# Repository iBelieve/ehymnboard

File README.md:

# eHymnBoard

A digital hymn board using e-ink screens. Designed and built by Michael Spencer and Christopher Spencer. First used in the Divine Service on Easter Sunday, A+D 2025.

This was a really interesting opportunity to explore how we might leverage modern technology in an anti-technology, anti-screens way. Hymn boards are a beautiful contrast to the modern trend of putting big distracting glowing screens in the front of the sanctuary by directing the congregation to a hymnal, a physical book with a collection of beloved time-tested hymns, a book that belongs not just in the sanctuary but in the home for daily family devotions.

The e-ink is as minimally distracting as possible. The screens have no light and do not glow at all; the e-ink particles combined with a matte finish makes them look "real" and "physical" and not digital or screen-like.They are updated once before the service and are literally powered off for the entire duration of the service (due to its physical nature, e-ink "holds" its content without power).

Looking for other projects that explore how modern technology can enhance tradition? Check out the [St. Martin Luther Zimbelstern](https://github.com/cmspencer109/Zimbelstern) by Christopher Spencer.

### Project Parts and Tech Stack

**Device**

The on-device code is responsible for driving the e-ink screens and handling the network communication with the server.

- Raspberry Pi Pico W
- [3x Waveshare 13.3" E-Paper HAT (K)](https://www.waveshare.com/product/ai/displays/e-paper/13.3inch-e-paper-hat-k.htm)
- Pico SDK
- C++

**Server**

The web app and backend for the eHymnBoard project.

- Python 3
- Flask
- Tailwind CSS
- daisyUI

Code is deployed to a [Hetzner VPS](https://www.hetzner.com/cloud/) using [Dokku](https://dokku.com).

**PCB Designs**

Custom PCBs that add picoblade connectors to the Pi Pico for the e-ink screens to connect to.

- KiCad 6

**CAD Designs**

CAD designs for the actual wood hymn board, the routing jig, and 3D printed standoffs for mounting all the circuit boards in the enclosure.

[OnShape CAD designs](https://cad.onshape.com/documents/b7beeccbdc2f765f30134b80/w/63d45aaa309ee02d139aa6aa/e/1ed80022fc77088e67dab883)

### Suppliers

No affiliation or sponsorship, just good suppliers we found.

- [Waveshare](https://www.waveshare.com/) - E-ink screens
- [DigiKey](https://www.digikey.com/) - Electronic components
- [JLCPCB](https://jlcpcb.com/) - PCB manufacturing
- [Woodchucks Wood](https://woodchuckswood.com/) - Wood for the boards

### License

- The device code is licensed under the [GNU General Public License v3.0 or later](https://www.gnu.org/licenses/gpl-3.0.en.html).
- The server code is licensed under the [GNU Affero General Public License v3.0 or later](https://www.gnu.org/licenses/agpl-3.0.en.html).
- The CAD models and PCB designs are licensed under the [CERN Open Hardware License v2 - Strongly Reciprocal](https://gitlab.com/ohwr/project/cernohl/-/wikis/uploads/819d71bea3458f71fba6cf4fb0f2de6b/cern_ohl_s_v2.txt).

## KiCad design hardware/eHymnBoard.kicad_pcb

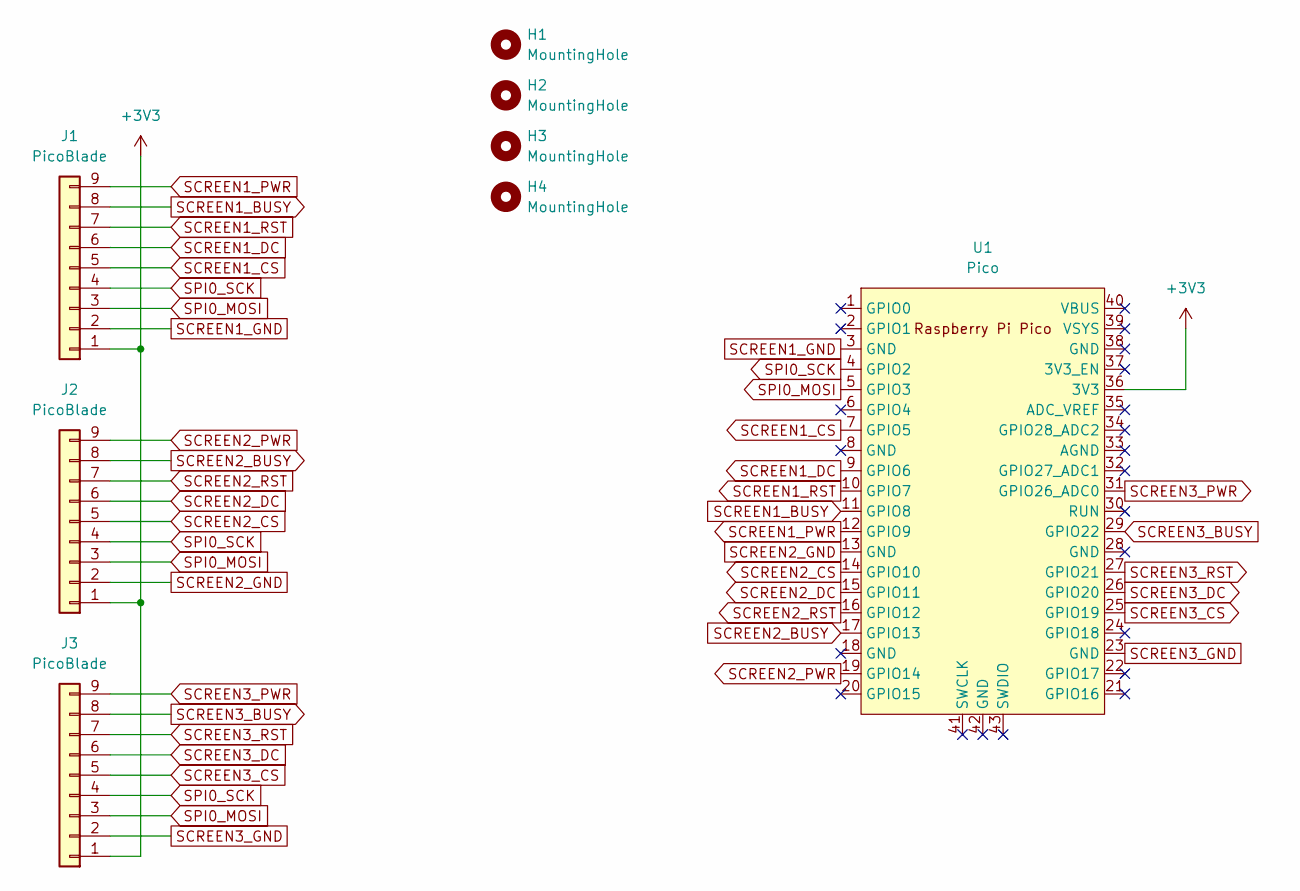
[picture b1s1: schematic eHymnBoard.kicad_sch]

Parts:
H1, H2, H3, H4: MountingHole; MountingHole_3mm
J1, J2, J3: PicoBlade; Molex_PicoBlade_53261-0971_1x09-1MP_P1.25mm_Horizontal
U1: Pico; RPi_Pico_SMD_TH

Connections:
+3V3: J1.1, J2.1, J3.1, U1.36 (3V3)
SCREEN1_BUSY: J1.8, U1.11 (GPIO8)
SCREEN1_CS: J1.5, U1.7 (GPIO5)
SCREEN1_DC: J1.6, U1.9 (GPIO6)
SCREEN1_GND: J1.2, U1.3 (GND)
SCREEN1_PWR: J1.9, U1.12 (GPIO9)
SCREEN1_RST: J1.7, U1.10 (GPIO7)
SCREEN2_BUSY: J2.8, U1.17 (GPIO13)
SCREEN2_CS: J2.5, U1.14 (GPIO10)
SCREEN2_DC: J2.6, U1.15 (GPIO11)
SCREEN2_GND: J2.2, U1.13 (GND)
SCREEN2_PWR: J2.9, U1.19 (GPIO14)
SCREEN2_RST: J2.7, U1.16 (GPIO12)
SCREEN3_BUSY: J3.8, U1.29 (GPIO22)
SCREEN3_CS: J3.5, U1.25 (GPIO19)
SCREEN3_DC: J3.6, U1.26 (GPIO20)
SCREEN3_GND: J3.2, U1.23 (GND)
SCREEN3_PWR: J3.9, U1.31 (GPIO26_ADC0)
SCREEN3_RST: J3.7, U1.27 (GPIO21)
SPI0_MOSI: J1.3, J2.3, J3.3, U1.5 (GPIO3)
SPI0_SCK: J1.4, J2.4, J3.4, U1.4 (GPIO2)

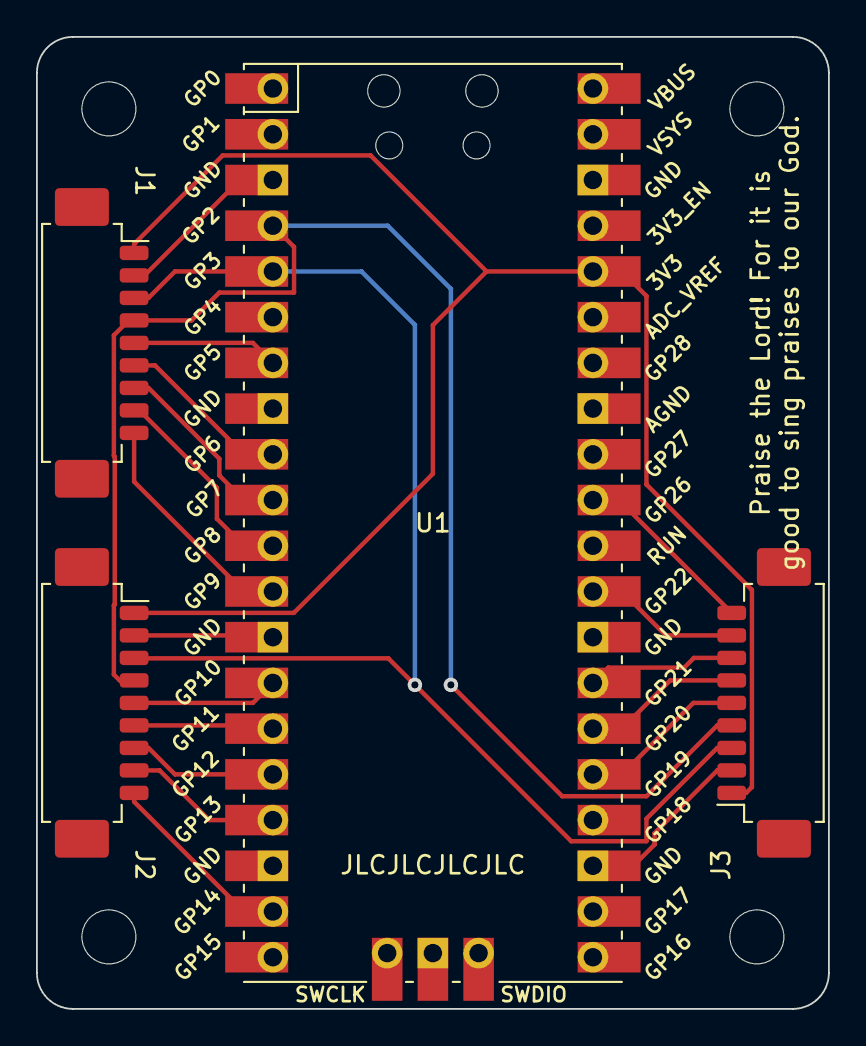
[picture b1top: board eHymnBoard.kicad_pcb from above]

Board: 2 copper layers, 44.0 x 54.0 mm, 8 parts (0 on the bottom side), 21 nets.

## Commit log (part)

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2025-04-22 Initial release for Easter 2025
2025-04-27 WiFi improvements
    - Track and connect to BSSID of specific WiFi result with strongest RSSI
    - Make 5 attempts every second to connect to a specific WiFi result
2025-05-11 Switch to sans serif font for better readability
2025-07-13 Mobile-friendly admin layout
2025-08-23 Fix spelling of Etag header - Cloudflare or something is changing it from ETag to Etag
2025-08-23 Show recently connected devices on the admin web page
2025-08-27 Set up watchdog to reboot after inactivity for 60 seconds
2025-08-27 Device code cleanup
2025-08-27 Ping healthchecks.io to track device uptime status
2025-09-27 Update outdated example secrets header
2025-09-27 Gracefully exit the monitor tool on Ctrl+C
2025-09-27 Update monitor script to auto-detect USB serial device on macOS
2025-09-27 Add README.md to device project
2025-09-28 Acquire async context lock for HTTP requests
2026-04-26 Improve serial monitor
